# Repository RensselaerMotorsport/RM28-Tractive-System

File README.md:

# RM28-TRACTIVE-SYSTEM

This respository currently contains several projects for Rensselaer Motorsport's RM28 FSAE competition car, along with some documentation, and spreadsheets for BOMs and calcs
* WIP RM28 Project - This project is the most up-to-date version of the 2024-2025 competition car's High Voltage System.

To open and work with these files, use the following software:
* LTSpice - Circuit simulation software used for preliminary mockups of circuit designs. The .asc files can be opened in other spice programs like ngspice or pspice, but these circuits were originally drafted in LTSpice
* KiCad - PCB design software used for creating schematics for manufacturing. These are either stored in .kicad_pcb files, or are gerber files packed away in zip archives
* Excel - For viewing of BSPD trip curve calculation sheet

Typical Circuits:
* Brake System Plausability Device (BSPD) - The custom circuit for RM28's safety circuit, designed to connect to our shutdown circuit. This is a fully analog safety circuit that activate the shutdown circuit when unsafe conditions (competition rules) are met.
    * The sensor values used for this circuit include the current sensor through the motor, and the voltage sensor from the accelerator pedal
    * See BSPD Current Sensor Trip Calculator.xlsx inside ./BSPD/ for calculations to determine the threshold voltage to activate this section of the circuit
* Ready to Move Light (RTML)
   * Blinking red LED if voltage outside accumulator is >60V, and if GLV on 
   * Static green LED if voltage outside accumulator is <60V, and if GLV on
* Voltage Indicator - Turns on LED indicator if voltage outside the accumulator container is greater than 60V. Must work in absence of GLV.
* ESF - Shows overall design of racecar electrical system. Includes datasheets, circuit diagrams, electrical architecture, and part numbers.

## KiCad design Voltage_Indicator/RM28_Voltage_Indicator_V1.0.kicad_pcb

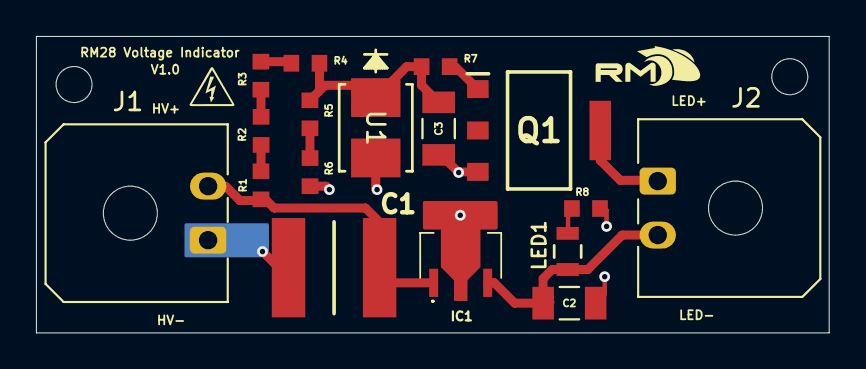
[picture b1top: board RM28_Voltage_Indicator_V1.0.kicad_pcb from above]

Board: 2 copper layers, 44.0 x 16.5 mm, 17 parts (0 on the bottom side), 11 nets.

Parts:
C1: 2.2μf; CAPC6153X670N
C2, C3: 22μf; CAPC3216X180N
IC1: NCP785AH120T1G; MC78L05ACHX_1
J1, J2: Molex_Micro-Fit_3.0_43650-0200_1x02_P3.00mm_Horiz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; Molex_Micro-Fit_3.0_43650-0200_1x02_P3.00mm_Horizontal
LED1: CMD17-21VRD/TR8; LED0805N_CML
Q1: SBCP56-16T1G; SOT230P700X175-4N
R1, R2, R3, R4: 240kΩ; RESC1608X55N
R5: 20kΩ; RESC1608X55N
R6, R8: 1kΩ; RESC1608X55N
R7: 10kΩ; RESC1608X55N
U1: 1SMB5927BT3G; SMB_ONS

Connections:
/+HV: C1.1, IC1.1 (VIN), J1.2, R1.1
GND: C1.2, C2.2, C3.2, IC1.2 (GND_1), IC1.4 (GND_2), J1.1, Q1.3 (E), R6.2, R8.2, U1.2 (ANODE)
unnamed: C2.1, IC1.3 (VOUT), J2.2, LED1.1
unnamed: LED1.2, R8.1
unnamed: Q1.1 (B), R7.2
unnamed: J2.1, Q1.4 (C_2)
unnamed: R1.2, R2.1
unnamed: R2.2, R3.1
unnamed: R3.2, R4.1
unnamed: R5.2, R6.1
unnamed: C3.1, R4.2, R5.1, R7.1, U1.1 (CATHODE)

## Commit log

2024-09-17 transferred readme from rm27 with updates for this year
2024-09-17 Fix README spelling
2024-09-27 Accumulator Indicator Schematic
2024-09-27 RM28 Accumulator Indicator Layout
2024-10-04 RM28 ESF V1.0 Draft
2024-10-04 RM28 Accu Indicator V1.0
2024-10-08 BSPD First Draft
    credit to Jacob W. for this initial draft
2024-10-08 change rail voltages throughout to match shutoff circuit logic
2024-10-11 RM28 Voltage indicator w/ trace fixes
2024-10-11 RM28 ESF w/ additional datasheets and precharge info
2024-10-18 Silkscreen changes, GLV side
2024-10-18 Fixed silkscreen on HV Side
2024-10-18 flip comparator circuit to standard orientation in BSPD
2024-10-18 limiting current draw by using realistic sensing resistances
2024-10-29 ROUGH DRAFT! Many changes to BSPD, mainly replacing 74 series OR-logic with analog components. VALUES ARE NOT ACCURATE RIGHT NOW!!!
2024-10-30 started implementing more changes for proper BSPD with current shutdown circuit design
2024-10-30 BSPD circuit topolgy fixed, logic is very close to working
2024-10-30 BSPD logic works! Need to tune to perfect window to be within rules, also need to switch to 5V logic with 12V output
2024-10-30 BSPD is in testable state, does not hold 12V once triggered, and does not use real world reference voltages yet
2024-10-30 misc BSPD fixes and comments, prev. issues still hold
2024-10-30 created latching relay, switch just needs to be modeled for simulation
2024-11-01 Updated RTML silkscreen
    Silkscreen now shows >4mm spacing
2024-11-01 RM28 Tractive System Schematic V1.0
2024-11-01 BSPD is fully functioning, many changes. Cannot simulate latching relay circuit
2024-11-08 Complete RM28 ESF V1.0
2024-11-08 RM28 Voltage Indicator V1.0
2024-11-08 Update README.md to include BSPD info.
    This file needs to be reworked a bit, still a bit wordy and confusing to an outsider looking to use this open sourced project
2024-11-08 reformated directory of this repo, easier to find individual project
2024-11-15 Changes to edgecuts and routing
2024-11-15 Silkscreen edits
2024-11-19 Layout updates
2024-11-19 Final changes for layout
2024-11-19 Added gerbers
2024-11-19 Update README.md with current existing circuits
2024-11-19 reorganization of misc files, more deleting more old files, matching file structure of readme
2024-11-22 Final layout changes
2024-11-30 Add more info & fix readability of README.md
2024-12-05 Test draft of RM27 FW
    Changed faults for battery health and thermistor disconnections
